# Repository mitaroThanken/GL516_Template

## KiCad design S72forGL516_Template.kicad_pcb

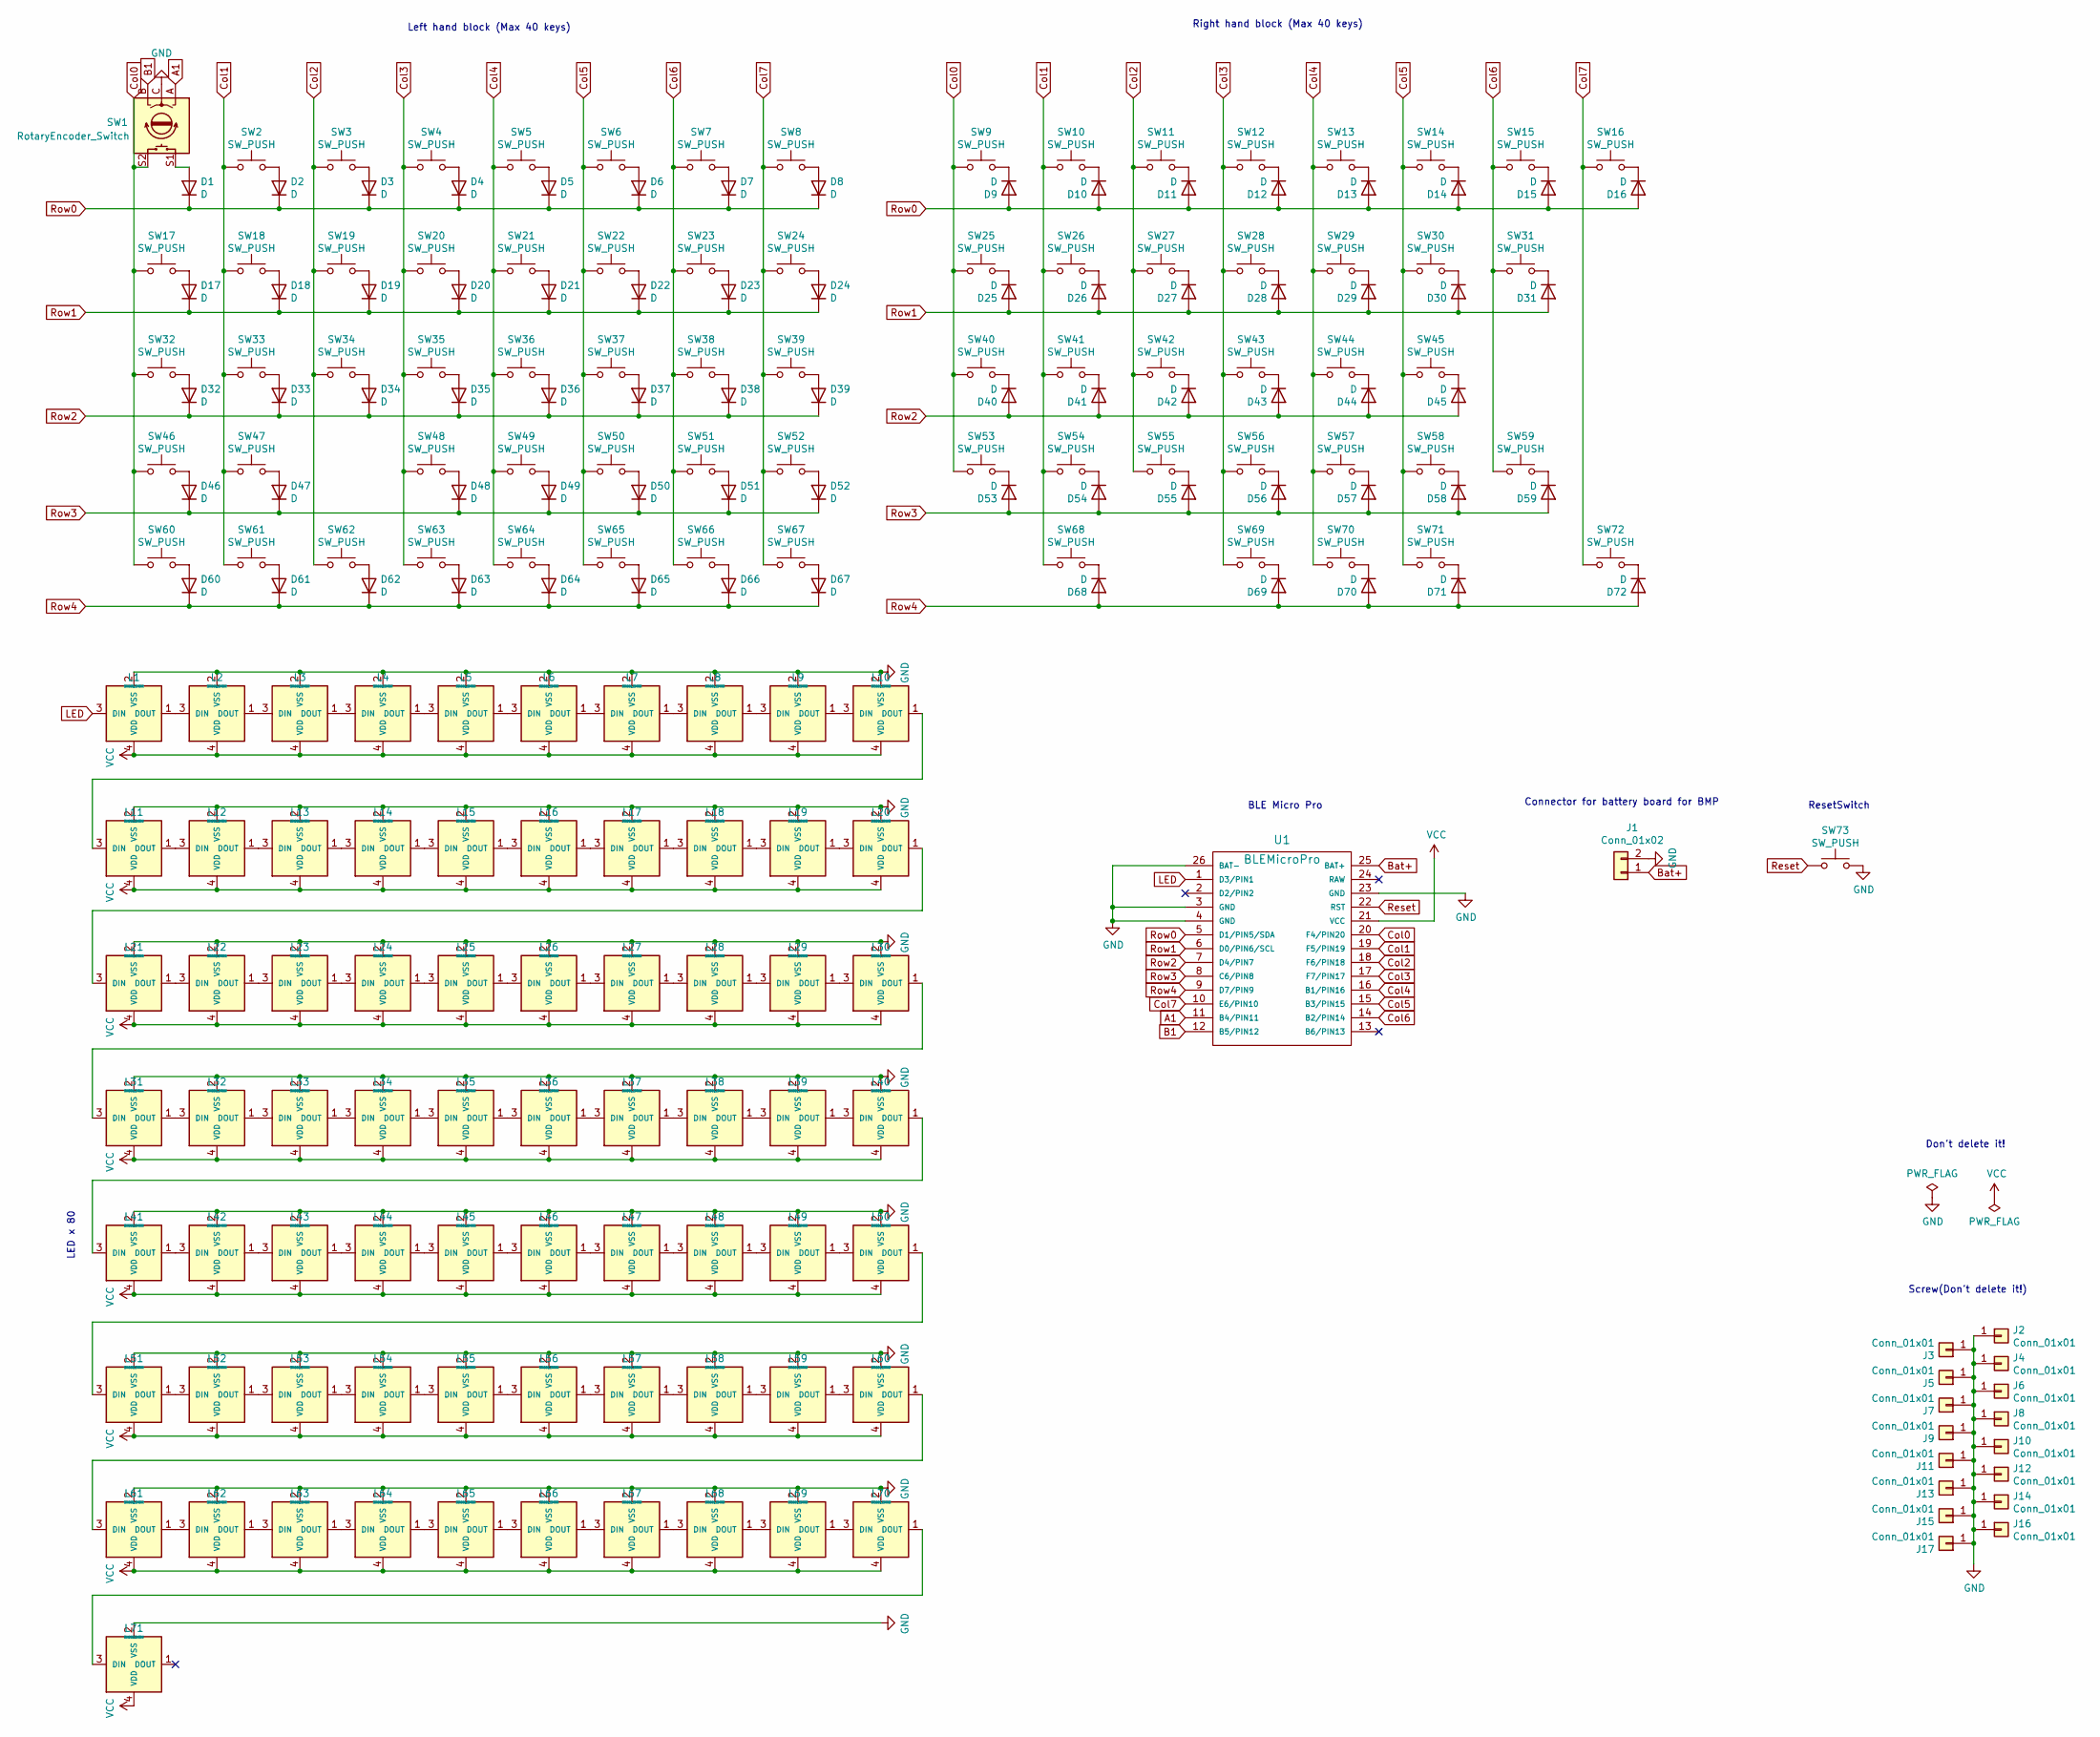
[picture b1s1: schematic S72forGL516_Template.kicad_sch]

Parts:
D1, D2, D3, D4, D5, D6, D7, D8, D9, D10, D11, D12, D13, D14, D15, D16, D17, D18, D19, D20, D21, D22, D23, D24, D25, D26, D27, D28, D29, D30, D31, D32, D33, D34, D35, D36, D37, D38, D39, D40, D41, D42, D43, D44, D45, D46, D47, D48, D49, D50, D51, D52, D53, D54, D55, D56, D57, D58, D59, D60, D61, D62, D63, D64, D65, D66, D67, D68, D69, D70, D71, D72: D; Diode_TH_SMD
J1: Conn_01x02; Battery_XH2.5_GL_PCB
J2, J4, J6, J8, J10, J12, J14, J15, J16, J17: Conn_01x01; m2_Screw_Hole_Fab
J3, J5, J7, J9, J11, J13: Conn_01x01; m2_Screw_Hole_EdgeCuts
L1, L2, L3, L4, L5, L6, L7, L8, L9, L10, L11, L12, L13, L14, L15, L16, L17, L18, L19, L20, L21, L22, L23, L24, L25, L26, L27, L28, L29, L30, L31, L32, L33, L34, L35, L36, L37, L38, L39, L40, L41, L42, L43, L44, L45, L46, L47, L48, L49, L50, L51, L52, L53, L54, L55, L56, L57, L58, L59, L60, L61, L62, L63, L64, L65, L66, L67, L68, L69, L70, L71: SK6812MINI; LED_SK6812MINI-E_BL
SW1: RotaryEncoder_Switch; RotaryEncoder_EC12E
SW2, SW3, SW4, SW5, SW6, SW7, SW8, SW9, SW10, SW11, SW12, SW13, SW14, SW15, SW16, SW17, SW19, SW20, SW21, SW22, SW23, SW24, SW25, SW26, SW27, SW28, SW29, SW30, SW32, SW34, SW35, SW36, SW37, SW38, SW39, SW40, SW41, SW42, SW43, SW44, SW45, SW46, SW48, SW49, SW50, SW51, SW52, SW53, SW54, SW55, SW56, SW57, SW58, SW60, SW64, SW65, SW66, SW67, SW72: SW_PUSH; CherryMX_Hotswap_1u
SW18, SW70, SW71: SW_PUSH; CherryMX_Hotswap_1.5u
SW31: SW_PUSH; CherryMX_Hotswap_ISO_Rev
SW33, SW59: SW_PUSH; CherryMX_Hotswap_1.75u
SW47: SW_PUSH; CherryMX_Hotswap_2.25u_Rev
SW61, SW62, SW63, SW69: SW_PUSH; CherryMX_Hotswap_1.25u
SW68: SW_PUSH; CherryMX_Hotswap_2u_Rev
SW73: SW_PUSH; ResetSW
U1: BLEMicroPro; Micon_BMP_GL

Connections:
A1: SW1.A, U1.11 (B4/PIN11)
B1: SW1.B, U1.12 (B5/PIN12)
Bat+: J1.1, U1.25 (BAT+)
Col0: SW1.S2, SW9.1, SW17.1, SW25.1, SW32.1, SW40.1, SW46.1, SW53.1, SW60.1, U1.20 (F4/PIN20)
Col1: SW2.1, SW10.1, SW18.1, SW26.1, SW33.1, SW41.1, SW47.1, SW54.1, SW61.1, SW68.1, U1.19 (F5/PIN19)
Col2: SW3.1, SW11.1, SW19.1, SW27.1, SW34.1, SW42.1, SW55.1, SW62.1, U1.18 (F6/PIN18)
Col3: SW4.1, SW12.1, SW20.1, SW28.1, SW35.1, SW43.1, SW48.1, SW56.1, SW63.1, SW69.1, U1.17 (F7/PIN17)
Col4: SW5.1, SW13.1, SW21.1, SW29.1, SW36.1, SW44.1, SW49.1, SW57.1, SW64.1, SW70.1, U1.16 (B1/PIN16)
Col5: SW6.1, SW14.1, SW22.1, SW30.1, SW37.1, SW45.1, SW50.1, SW58.1, SW65.1, SW71.1, U1.15 (B3/PIN15)
Col6: SW7.1, SW15.1, SW23.1, SW31.1, SW38.1, SW51.1, SW59.1, SW66.1, U1.14 (B2/PIN14)
Col7: SW8.1, SW16.1, SW24.1, SW39.1, SW52.1, SW67.1, SW72.1, U1.10 (E6/PIN10)
GND: J1.2, J2.1, J3.1, J4.1, J5.1, J6.1, J7.1, J8.1, J9.1, J10.1, J11.1, J12.1, J13.1, J14.1, J15.1, J16.1, J17.1, L1.2 (VSS), L2.2 (VSS), L3.2 (VSS), L4.2 (VSS), L5.2 (VSS), L6.2 (VSS), L7.2 (VSS), L8.2 (VSS), L9.2 (VSS), L10.2 (VSS), L11.2 (VSS), L12.2 (VSS), L13.2 (VSS), L14.2 (VSS), L15.2 (VSS), L16.2 (VSS), L17.2 (VSS), L18.2 (VSS), L19.2 (VSS), L20.2 (VSS), L21.2 (VSS), L22.2 (VSS), L23.2 (VSS), L24.2 (VSS), L25.2 (VSS), L26.2 (VSS), L27.2 (VSS), L28.2 (VSS), L29.2 (VSS), L30.2 (VSS), L31.2 (VSS), L32.2 (VSS), L33.2 (VSS), L34.2 (VSS), L35.2 (VSS), L36.2 (VSS), L37.2 (VSS), L38.2 (VSS), L39.2 (VSS), L40.2 (VSS), L41.2 (VSS), L42.2 (VSS), L43.2 (VSS), L44.2 (VSS), L45.2 (VSS), L46.2 (VSS), L47.2 (VSS), L48.2 (VSS), L49.2 (VSS), L50.2 (VSS), L51.2 (VSS), L52.2 (VSS), L53.2 (VSS), L54.2 (VSS), L55.2 (VSS), L56.2 (VSS), L57.2 (VSS), L58.2 (VSS), L59.2 (VSS), L60.2 (VSS), L61.2 (VSS), L62.2 (VSS), L63.2 (VSS), L64.2 (VSS), L65.2 (VSS), L66.2 (VSS), L67.2 (VSS), L68.2 (VSS), L69.2 (VSS), L70.2 (VSS), L71.2 (VSS), SW1.C, SW73.2, U1.3 (GND), U1.4 (GND), U1.23 (GND), U1.26 (BAT-)
LED: L1.3 (DIN), U1.1 (D3/PIN1)
unnamed: D2.2 (A), SW2.2
unnamed: D3.2 (A), SW3.2
unnamed: D4.2 (A), SW4.2
unnamed: D5.2 (A), SW5.2
unnamed: D6.2 (A), SW6.2
unnamed: D7.2 (A), SW7.2
unnamed: D8.2 (A), SW8.2
unnamed: D9.1 (K), SW9.2
unnamed: D10.1 (K), SW10.2
unnamed: D11.1 (K), SW11.2
unnamed: D12.1 (K), SW12.2
unnamed: D14.1 (K), SW14.2
unnamed: D15.1 (K), SW15.2
unnamed: D16.1 (K), SW16.2
unnamed: D17.2 (A), SW17.2
unnamed: D18.2 (A), SW18.2
unnamed: D19.2 (A), SW19.2
unnamed: D20.2 (A), SW20.2
unnamed: D21.2 (A), SW21.2
unnamed: D22.2 (A), SW22.2
unnamed: D23.2 (A), SW23.2
unnamed: D24.2 (A), SW24.2
unnamed: D25.1 (K), SW25.2
unnamed: D26.1 (K), SW26.2
unnamed: D27.1 (K), SW27.2
unnamed: D28.1 (K), SW28.2
unnamed: D29.1 (K), SW29.2
unnamed: D30.1 (K), SW30.2
unnamed: D31.1 (K), SW31.2
unnamed: D32.2 (A), SW32.2
unnamed: D33.2 (A), SW33.2
unnamed: D34.2 (A), SW34.2
unnamed: D35.2 (A), SW35.2
unnamed: D36.2 (A), SW36.2
unnamed: D37.2 (A), SW37.2
unnamed: D38.2 (A), SW38.2
unnamed: D39.2 (A), SW39.2
unnamed: D40.1 (K), SW40.2
unnamed: D41.1 (K), SW41.2
unnamed: D42.1 (K), SW42.2
unnamed: D43.1 (K), SW43.2
unnamed: D44.1 (K), SW44.2
unnamed: D45.1 (K), SW45.2
unnamed: D46.2 (A), SW46.2
unnamed: D47.2 (A), SW47.2
unnamed: D48.2 (A), SW48.2
unnamed: D49.2 (A), SW49.2
unnamed: D50.2 (A), SW50.2
unnamed: D51.2 (A), SW51.2
unnamed: D52.2 (A), SW52.2
unnamed: D53.1 (K), SW53.2
unnamed: D54.1 (K), SW54.2
unnamed: D55.1 (K), SW55.2
unnamed: D56.1 (K), SW56.2
unnamed: D57.1 (K), SW57.2
unnamed: D58.1 (K), SW58.2
unnamed: D59.1 (K), SW59.2
unnamed: D60.2 (A), SW60.2
unnamed: D61.2 (A), SW61.2
unnamed: D62.2 (A), SW62.2
unnamed: D63.2 (A), SW63.2
unnamed: D64.2 (A), SW64.2
unnamed: D65.2 (A), SW65.2
unnamed: D66.2 (A), SW66.2
unnamed: D67.2 (A), SW67.2
unnamed: D68.1 (K), SW68.2
unnamed: D69.1 (K), SW69.2
unnamed: D70.1 (K), SW70.2
unnamed: D71.1 (K), SW71.2
unnamed: D72.1 (K), SW72.2
unnamed: L1.1 (DOUT), L2.3 (DIN)
unnamed: L2.1 (DOUT), L3.3 (DIN)
unnamed: L3.1 (DOUT), L4.3 (DIN)
unnamed: L4.1 (DOUT), L5.3 (DIN)
unnamed: L5.1 (DOUT), L6.3 (DIN)
unnamed: L6.1 (DOUT), L7.3 (DIN)
unnamed: L7.1 (DOUT), L8.3 (DIN)
unnamed: L8.1 (DOUT), L9.3 (DIN)
unnamed: L10.1 (DOUT), L11.3 (DIN)
unnamed: L9.1 (DOUT), L10.3 (DIN)
unnamed: L11.1 (DOUT), L12.3 (DIN)
unnamed: L12.1 (DOUT), L13.3 (DIN)
unnamed: L13.1 (DOUT), L14.3 (DIN)
unnamed: L14.1 (DOUT), L15.3 (DIN)
unnamed: L15.1 (DOUT), L16.3 (DIN)
unnamed: L16.1 (DOUT), L17.3 (DIN)
unnamed: L17.1 (DOUT), L18.3 (DIN)
unnamed: L18.1 (DOUT), L19.3 (DIN)
unnamed: L19.1 (DOUT), L20.3 (DIN)
unnamed: L20.1 (DOUT), L21.3 (DIN)
unnamed: L21.1 (DOUT), L22.3 (DIN)
unnamed: L22.1 (DOUT), L23.3 (DIN)
unnamed: L23.1 (DOUT), L24.3 (DIN)
unnamed: L24.1 (DOUT), L25.3 (DIN)
unnamed: L25.1 (DOUT), L26.3 (DIN)
unnamed: L26.1 (DOUT), L27.3 (DIN)
unnamed: L27.1 (DOUT), L28.3 (DIN)
unnamed: L28.1 (DOUT), L29.3 (DIN)
unnamed: L29.1 (DOUT), L30.3 (DIN)
unnamed: L30.1 (DOUT), L31.3 (DIN)
unnamed: L31.1 (DOUT), L32.3 (DIN)
unnamed: L32.1 (DOUT), L33.3 (DIN)
unnamed: L33.1 (DOUT), L34.3 (DIN)
unnamed: L34.1 (DOUT), L35.3 (DIN)
unnamed: L35.1 (DOUT), L36.3 (DIN)
unnamed: L36.1 (DOUT), L37.3 (DIN)
unnamed: L37.1 (DOUT), L38.3 (DIN)
unnamed: L38.1 (DOUT), L39.3 (DIN)
unnamed: L39.1 (DOUT), L40.3 (DIN)
unnamed: L40.1 (DOUT), L41.3 (DIN)
unnamed: L41.1 (DOUT), L42.3 (DIN)
unnamed: L42.1 (DOUT), L43.3 (DIN)
unnamed: L43.1 (DOUT), L44.3 (DIN)
unnamed: L44.1 (DOUT), L45.3 (DIN)
unnamed: L45.1 (DOUT), L46.3 (DIN)
unnamed: L46.1 (DOUT), L47.3 (DIN)
unnamed: L47.1 (DOUT), L48.3 (DIN)
unnamed: L48.1 (DOUT), L49.3 (DIN)
unnamed: L49.1 (DOUT), L50.3 (DIN)
unnamed: L50.1 (DOUT), L51.3 (DIN)
unnamed: L51.1 (DOUT), L52.3 (DIN)
unnamed: L52.1 (DOUT), L53.3 (DIN)
unnamed: L53.1 (DOUT), L54.3 (DIN)
unnamed: L54.1 (DOUT), L55.3 (DIN)
unnamed: L55.1 (DOUT), L56.3 (DIN)
unnamed: L56.1 (DOUT), L57.3 (DIN)
unnamed: L57.1 (DOUT), L58.3 (DIN)
unnamed: L58.1 (DOUT), L59.3 (DIN)
unnamed: L59.1 (DOUT), L60.3 (DIN)
unnamed: L60.1 (DOUT), L61.3 (DIN)
unnamed: L61.1 (DOUT), L62.3 (DIN)
unnamed: L62.1 (DOUT), L63.3 (DIN)
unnamed: L63.1 (DOUT), L64.3 (DIN)
unnamed: L64.1 (DOUT), L65.3 (DIN)
unnamed: L65.1 (DOUT), L66.3 (DIN)
unnamed: L66.1 (DOUT), L67.3 (DIN)
unnamed: L67.1 (DOUT), L68.3 (DIN)
unnamed: L68.1 (DOUT), L69.3 (DIN)
unnamed: L69.1 (DOUT), L70.3 (DIN)
unnamed: L70.1 (DOUT), L71.3 (DIN)
unnamed: D1.2 (A), SW1.S1
unnamed: D13.1 (K), SW13.2
Reset: SW73.1, U1.22 (RST)
Row0: D1.1 (K), D2.1 (K), D3.1 (K), D4.1 (K), D5.1 (K), D6.1 (K), D7.1 (K), D8.1 (K), D9.2 (A), D10.2 (A), D11.2 (A), D12.2 (A), D13.2 (A), D14.2 (A), D15.2 (A), D16.2 (A), U1.5 (D1/PIN5/SDA)
Row1: D17.1 (K), D18.1 (K), D19.1 (K), D20.1 (K), D21.1 (K), D22.1 (K), D23.1 (K), D24.1 (K), D25.2 (A), D26.2 (A), D27.2 (A), D28.2 (A), D29.2 (A), D30.2 (A), D31.2 (A), U1.6 (D0/PIN6/SCL)
Row2: D32.1 (K), D33.1 (K), D34.1 (K), D35.1 (K), D36.1 (K), D37.1 (K), D38.1 (K), D39.1 (K), D40.2 (A), D41.2 (A), D42.2 (A), D43.2 (A), D44.2 (A), D45.2 (A), U1.7 (D4/PIN7)
Row3: D46.1 (K), D47.1 (K), D48.1 (K), D49.1 (K), D50.1 (K), D51.1 (K), D52.1 (K), D53.2 (A), D54.2 (A), D55.2 (A), D56.2 (A), D57.2 (A), D58.2 (A), D59.2 (A), U1.8 (C6/PIN8)
Row4: D60.1 (K), D61.1 (K), D62.1 (K), D63.1 (K), D64.1 (K), D65.1 (K), D66.1 (K), D67.1 (K), D68.2 (A), D69.2 (A), D70.2 (A), D71.2 (A), D72.2 (A), U1.9 (D7/PIN9)
VCC: L1.4 (VDD), L2.4 (VDD), L3.4 (VDD), L4.4 (VDD), L5.4 (VDD), L6.4 (VDD), L7.4 (VDD), L8.4 (VDD), L9.4 (VDD), L10.4 (VDD), L11.4 (VDD), L12.4 (VDD), L13.4 (VDD), L14.4 (VDD), L15.4 (VDD), L16.4 (VDD), L17.4 (VDD), L18.4 (VDD), L19.4 (VDD), L20.4 (VDD), L21.4 (VDD), L22.4 (VDD), L23.4 (VDD), L24.4 (VDD), L25.4 (VDD), L26.4 (VDD), L27.4 (VDD), L28.4 (VDD), L29.4 (VDD), L30.4 (VDD), L31.4 (VDD), L32.4 (VDD), L33.4 (VDD), L34.4 (VDD), L35.4 (VDD), L36.4 (VDD), L37.4 (VDD), L38.4 (VDD), L39.4 (VDD), L40.4 (VDD), L41.4 (VDD), L42.4 (VDD), L43.4 (VDD), L44.4 (VDD), L45.4 (VDD), L46.4 (VDD), L47.4 (VDD), L48.4 (VDD), L49.4 (VDD), L50.4 (VDD), L51.4 (VDD), L52.4 (VDD), L53.4 (VDD), L54.4 (VDD), L55.4 (VDD), L56.4 (VDD), L57.4 (VDD), L58.4 (VDD), L59.4 (VDD), L60.4 (VDD), L61.4 (VDD), L62.4 (VDD), L63.4 (VDD), L64.4 (VDD), L65.4 (VDD), L66.4 (VDD), L67.4 (VDD), L68.4 (VDD), L69.4 (VDD), L70.4 (VDD), L71.4 (VDD), U1.21 (VCC)

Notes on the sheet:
BLE Micro Pro
Don't delete it!
Left hand block (Max 40 keys)
Screw(Don't delete it!)
Connector for battery board for BMP
ResetSwitch
LED x 80
Right hand block (Max 40 keys)

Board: 2 copper layers, 218 parts (0 on the bottom side), 162 nets, no tracks yet.

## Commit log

2022-01-09 ファイル名を変更
2022-01-09 add .gitignore
2022-01-09 スイッチプレート作ってみる
2022-01-09 [WIP] 実装プレートを作る
    KiCad 6.0 で保存しなおしただけの状態。
2022-01-09 [FIX] キーの連番、デザインガイドと縦横逆に振ってしまっていた
    回路図上、LEDを回転・反転して、アノテーションを振りなおした。
2022-01-09 キースイッチとLEDの数を調整
2022-01-09 左上隅をロータリーエンコーダにしてみた
2022-01-09 フットプリントを紐づけ
2022-01-09 フットプリントを配置
2022-01-09 VCCネットクラスを追加
